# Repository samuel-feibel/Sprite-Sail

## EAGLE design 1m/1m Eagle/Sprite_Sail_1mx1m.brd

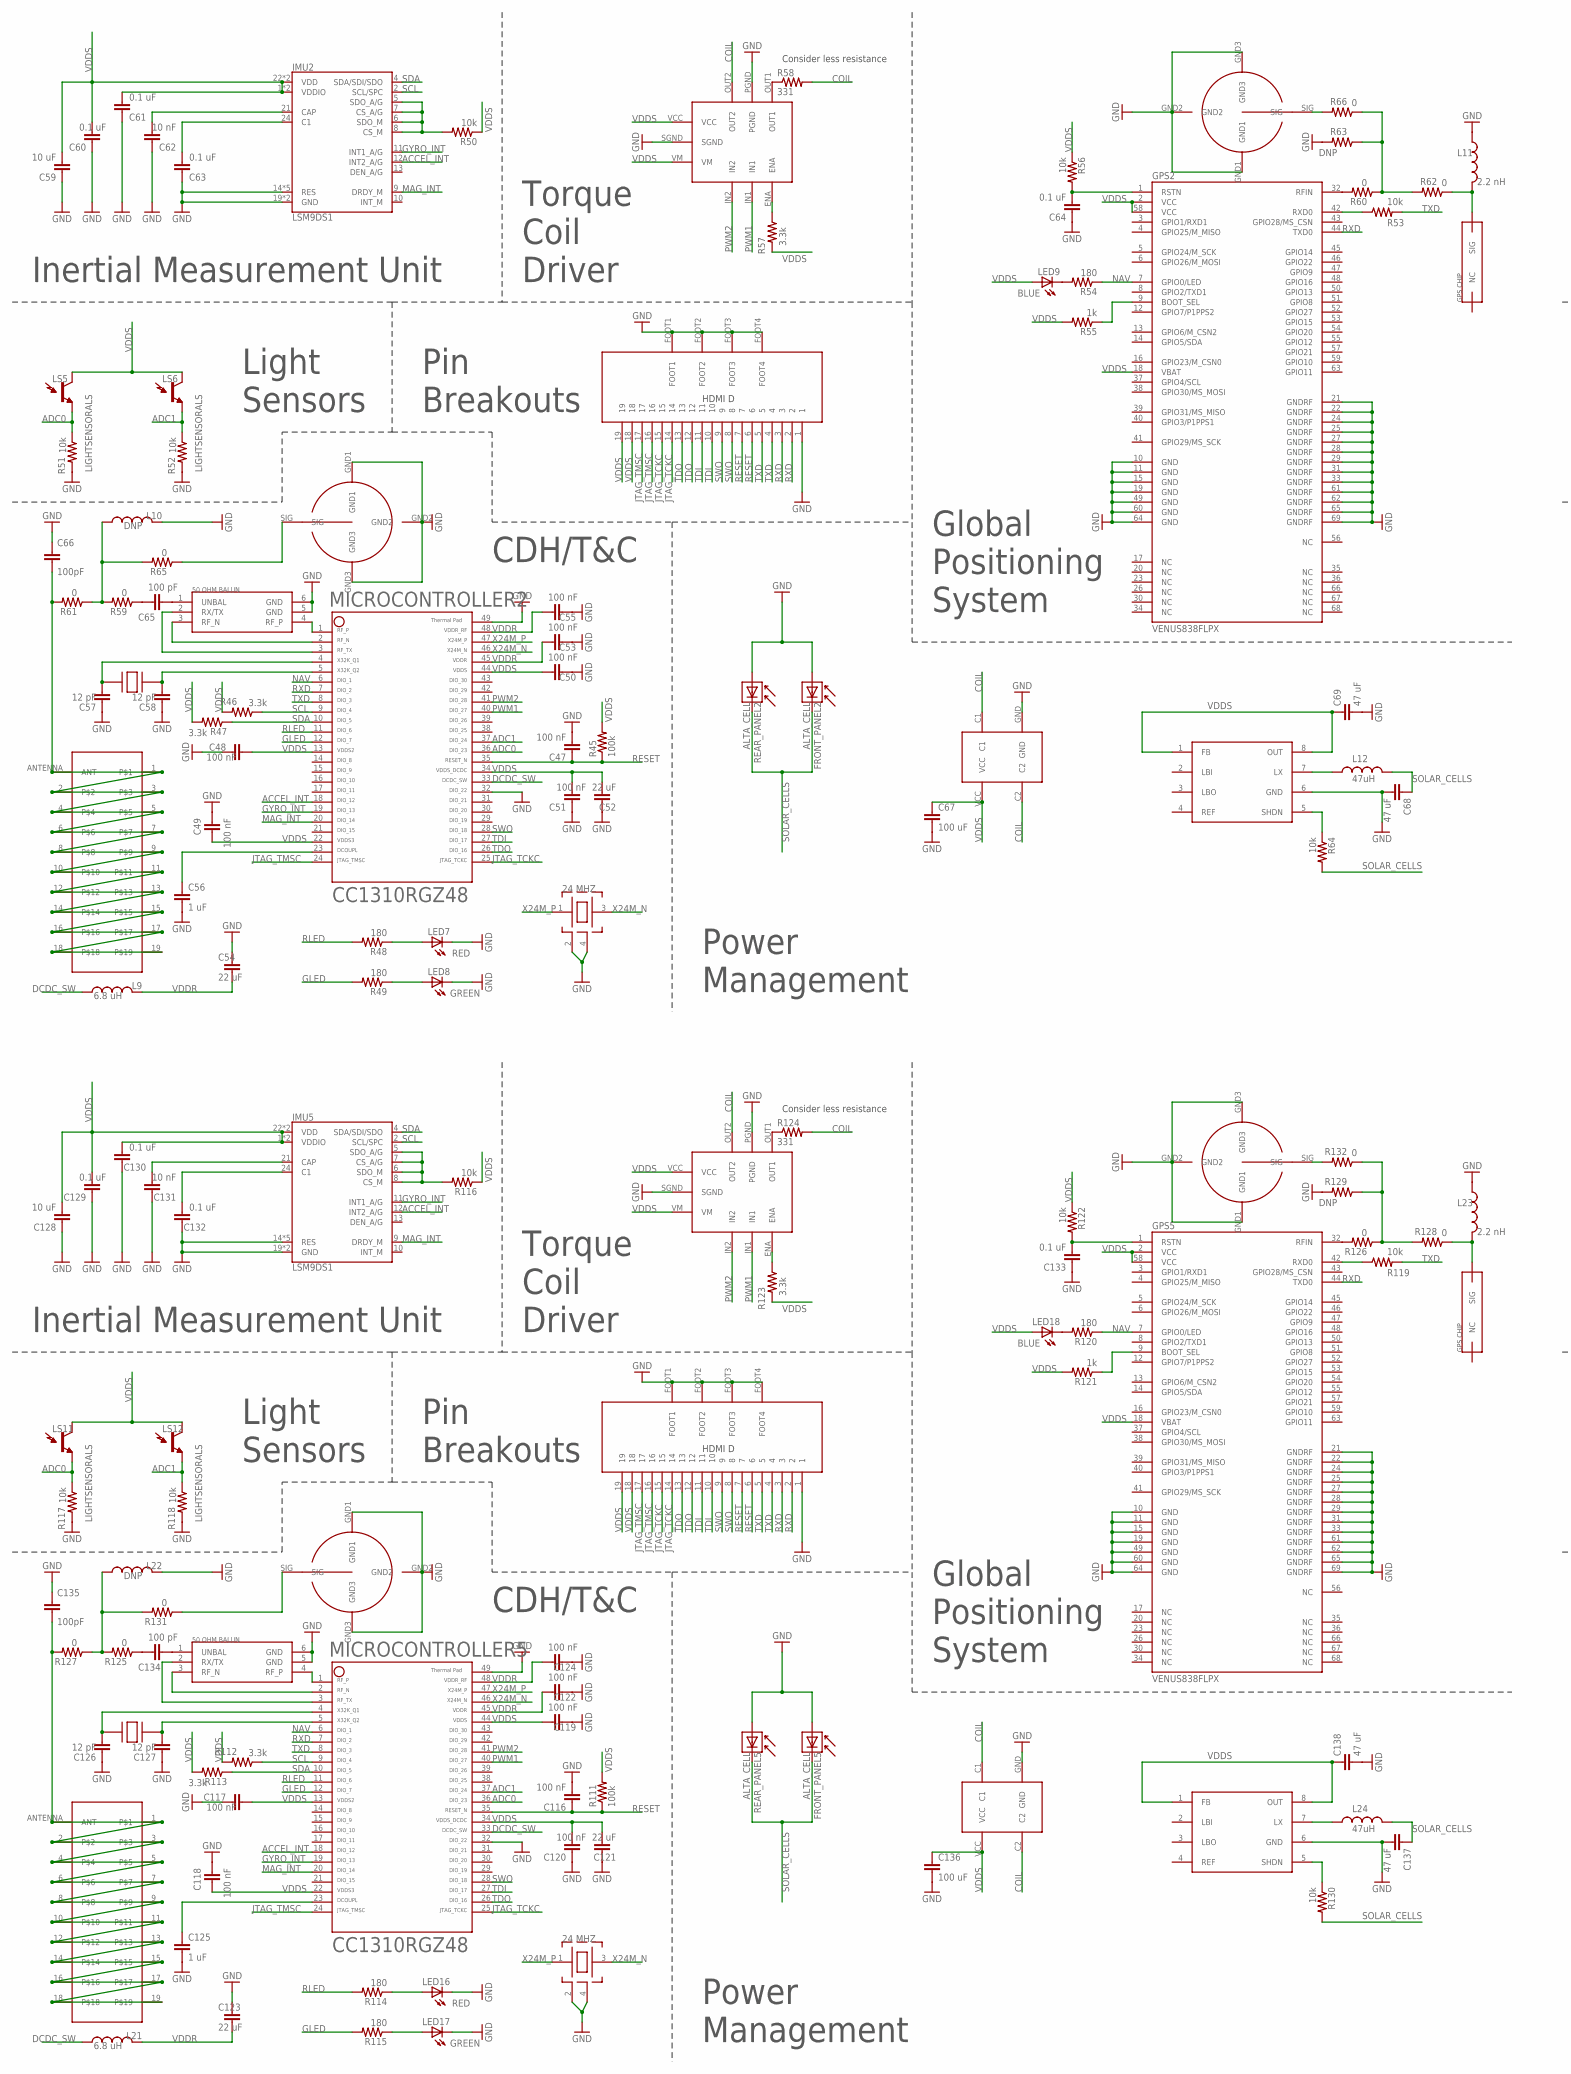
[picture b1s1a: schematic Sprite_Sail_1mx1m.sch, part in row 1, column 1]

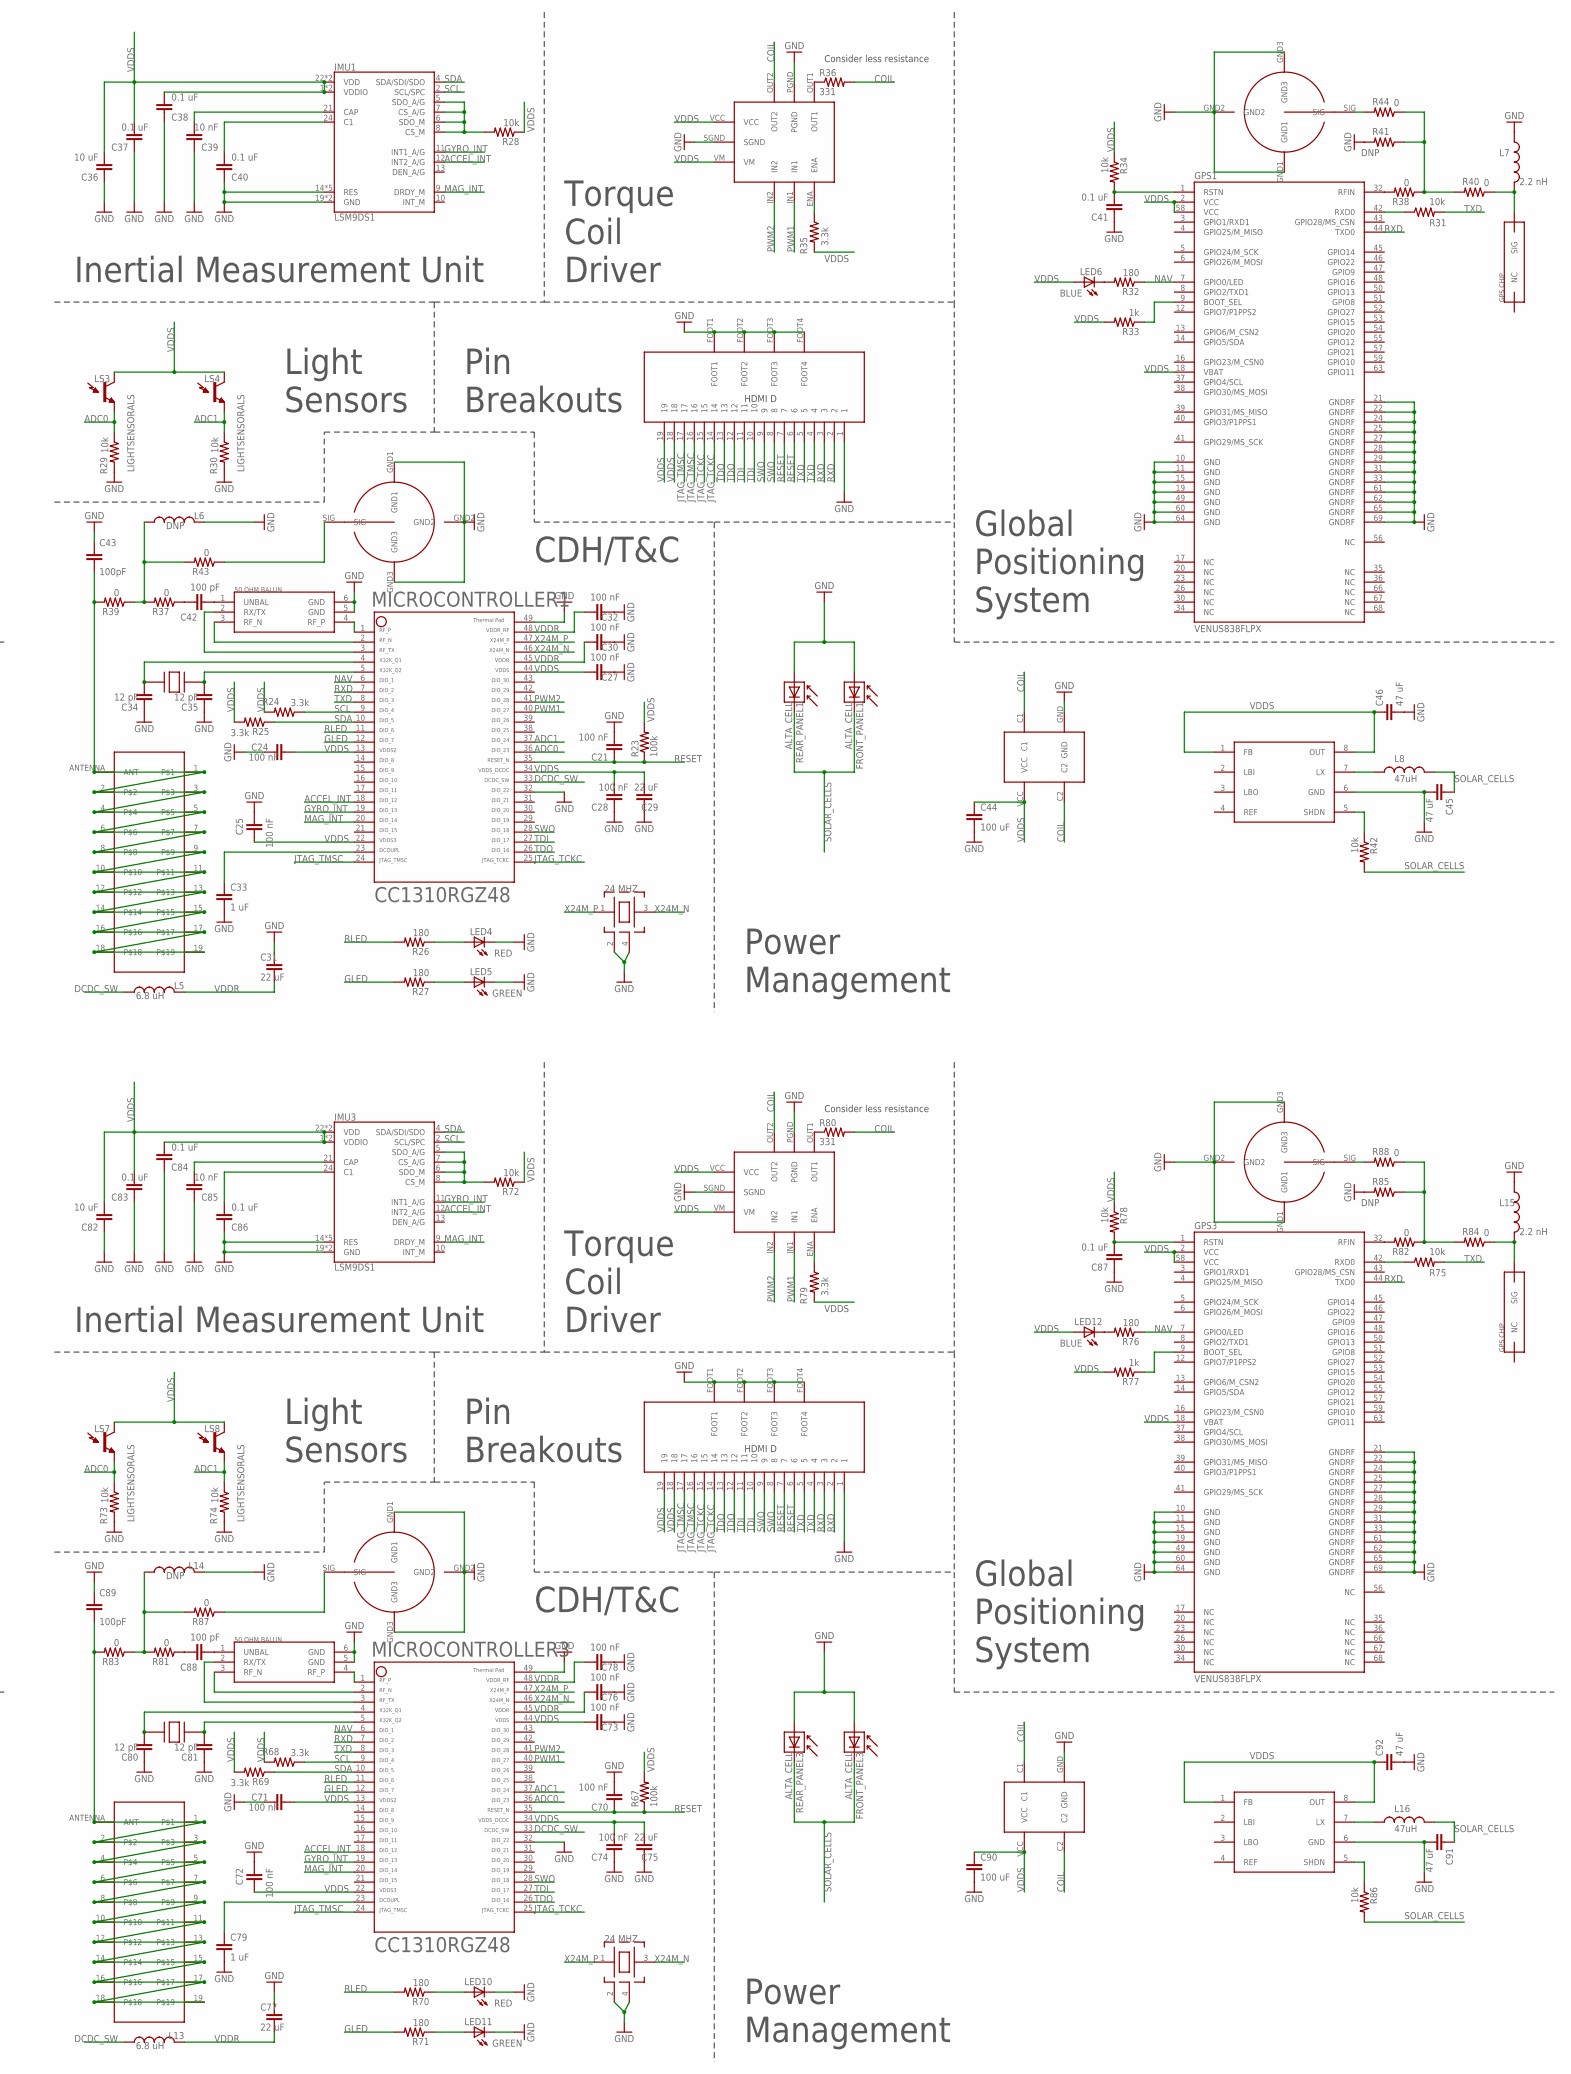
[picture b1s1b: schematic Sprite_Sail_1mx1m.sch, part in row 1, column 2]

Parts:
32.1, 32.2, 32.3, 32.5: FC-135
BALUN1, BALUN2, BALUN3, BALUN5: JOHANSON_BALUN
C21, C24, C25, C27, C28, C30, C32, C47, C48, C49, C50, C51, C53, C55, C70, C71, C72, C73, C74, C76, C78, C116, C117, C118, C119, C120, C122, C124: 100 nF; 0402-CAP
C29, C31, C52, C54, C75, C77, C121, C123: 22 uF; 0402-CAP
C33, C56, C79, C125: 1 uF; 0402-CAP
C34, C35, C57, C58, C80, C81, C126, C127: 12 pF; 0402-CAP
C36, C59, C82, C128: 10 uF; 0402-CAP
C37, C38, C40, C41, C60, C61, C63, C64, C83, C84, C86, C87, C129, C130, C132, C133: 0.1 uF; 0402-CAP
C39, C62, C85, C131: 10 nF; 0402-CAP
C42, C65, C88, C134: 100 pF; 0402-CAP
C43, C66, C89, C135: 100pF; 0603-CAP
C44, C67, C90, C136: 100 uF; 0805
C45, C46, C68, C69, C91, C92, C137, C138: 47 uF; 0805
FRONT_PANEL1, FRONT_PANEL2, FRONT_PANEL3, FRONT_PANEL5: ALTA_CELL
GPS1, GPS2, GPS3, GPS5: VENUS838FLPX
IMU1, IMU2, IMU3, IMU5: LSM9DS1; LGA24-8X4
L5, L9, L13, L21: 6.8 uH; 0603
L6, L10, L14, L22: DNP; 0603
L7, L11, L15, L23: 2.2 nH; 0603
L8, L12, L16, L24: 47uH; 0603
LED4, LED7, LED10, LED16: RED; LED-0603
LED5, LED8, LED11, LED17: GREEN; LED-0603
LED6, LED9, LED12, LED18: BLUE; LED-0603
LS3, LS4, LS5, LS6, LS7, LS8, LS11, LS12: LIGHTSENSORALS; ALS-PT19
MICROCONTROLLER1, MICROCONTROLLER2, MICROCONTROLLER3, MICROCONTROLLER5: CC1310
R23, R45, R67, R111: 100k; 0402-RES
R24, R25, R35, R46, R47, R57, R68, R69, R79, R112, R113, R123: 3.3k; 0402-RES
R26, R27, R32, R48, R49, R54, R70, R71, R76, R114, R115, R120: 180; 0402-RES
R28, R29, R30, R31, R34, R42, R50, R51, R52, R53, R56, R64, R72, R73, R74, R75, R78, R86, R116, R117, R118, R119, R122, R130: 10k; 0402-RES
R33, R55, R77, R121: 1k; 0402-RES
R36, R58, R80, R124: 331; 0402-RES
R37, R38, R39, R40, R43, R44, R59, R60, R61, R62, R65, R66, R81, R82, R83, R84, R87, R88, R125, R126, R127, R128, R131, R132: 0; 0603-RES
R41, R63, R85, R129: DNP; 0603-RES
REAR_PANEL1, REAR_PANEL2, REAR_PANEL3, REAR_PANEL5: ALTA_CELL
TSX1, TSX2, TSX3, TSX5: TSX-3225
U$1, U$17, U$25, U$41: LV8417CS
U$10, U$18, U$26, U$42: JOHANSON_GPS_CHIP
U$11, U$19, U$27, U$43: PANASONIC_RECTIFIER
U$12, U$20, U$28, U$44: PCB_ANTENNA
U$13, U$14, U$21, U$22, U$29, U$30, U$45, U$46: MM5329-2700; MM5829-2700
U$15, U$23, U$31, U$47: L6920
U$16, U$24, U$32, U$48: HDMID

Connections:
ACCEL_INT: IMU1.12 (INT2_A/G), IMU2.12 (INT2_A/G), IMU3.12 (INT2_A/G), IMU5.12 (INT2_A/G), MICROCONTROLLER1.18, MICROCONTROLLER2.18, MICROCONTROLLER3.18, MICROCONTROLLER5.18
ADC0: LS3.E (E1), LS5.E (E1), LS7.E (E1), LS11.E (E1), MICROCONTROLLER1.36, MICROCONTROLLER2.36, MICROCONTROLLER3.36, MICROCONTROLLER5.36, R29.1, R51.1, R73.1, R117.1
ADC1: LS4.E (E1), LS6.E (E1), LS8.E (E1), LS12.E (E1), MICROCONTROLLER1.37, MICROCONTROLLER2.37, MICROCONTROLLER3.37, MICROCONTROLLER5.37, R30.1, R52.1, R74.1, R118.1
ANTENNA1: C43.2, R39.2, U$12.1, U$12.2, U$12.3, U$12.4, U$12.5, U$12.6, U$12.7, U$12.8, U$12.9, U$12.10, U$12.11, U$12.12, U$12.13, U$12.14, U$12.15, U$12.16, U$12.17, U$12.18, U$12.19, U$12.ANTENNA (ANT)
ANTENNA2: C66.2, R61.2, U$20.1, U$20.2, U$20.3, U$20.4, U$20.5, U$20.6, U$20.7, U$20.8, U$20.9, U$20.10, U$20.11, U$20.12, U$20.13, U$20.14, U$20.15, U$20.16, U$20.17, U$20.18, U$20.19, U$20.ANTENNA (ANT)
ANTENNA3: C89.2, R83.2, U$28.1, U$28.2, U$28.3, U$28.4, U$28.5, U$28.6, U$28.7, U$28.8, U$28.9, U$28.10, U$28.11, U$28.12, U$28.13, U$28.14, U$28.15, U$28.16, U$28.17, U$28.18, U$28.19, U$28.ANTENNA (ANT)
ANTENNA5: C135.2, R127.2, U$44.1, U$44.2, U$44.3, U$44.4, U$44.5, U$44.6, U$44.7, U$44.8, U$44.9, U$44.10, U$44.11, U$44.12, U$44.13, U$44.14, U$44.15, U$44.16, U$44.17, U$44.18, U$44.19, U$44.ANTENNA (ANT)
COIL: R36.2, R58.2, R80.2, R124.2, U$1.OUT2, U$11.C1, U$11.C2, U$17.OUT2, U$19.C1, U$19.C2, U$25.OUT2, U$27.C1, U$27.C2, U$41.OUT2, U$43.C1, U$43.C2
DCDC_SW: L5.1, L9.1, L13.1, L21.1, MICROCONTROLLER1.33, MICROCONTROLLER2.33, MICROCONTROLLER3.33, MICROCONTROLLER5.33
GLED: MICROCONTROLLER1.12, MICROCONTROLLER2.12, MICROCONTROLLER3.12, MICROCONTROLLER5.12, R27.2, R49.2, R71.2, R115.2
GND: BALUN1.5 (GND), BALUN1.6 (GND), BALUN2.5 (GND), BALUN2.6 (GND), BALUN3.5 (GND), BALUN3.6 (GND), BALUN5.5 (GND), BALUN5.6 (GND), C21.2, C24.2, C25.2, C27.2, C28.2, C29.2, C30.2, C31.2, C32.2, C33.2, C34.2, C35.2, C36.2, C37.2, C38.2, C39.2, C40.2, C41.2, C43.1, C44.2, C45.2, C46.2, C47.2, C48.2, C49.2, C50.2, C51.2, C52.2, C53.2, C54.2, C55.2, C56.2, C57.2, C58.2, C59.2, C60.2, C61.2, C62.2, C63.2, C64.2, C66.1, C67.2, C68.2, C69.2, C70.2, C71.2, C72.2, C73.2, C74.2, C75.2, C76.2, C77.2, C78.2, C79.2, C80.2, C81.2, C82.2, C83.2, C84.2, C85.2, C86.2, C87.2, C89.1, C90.2, C91.2, C92.2, C116.2, C117.2, C118.2, C119.2, C120.2, C121.2, C122.2, C123.2, C124.2, C125.2, C126.2, C127.2, C128.2, C129.2, C130.2, C131.2, C132.2, C133.2, C135.1, C136.2, C137.2, C138.2, FRONT_PANEL1.-, FRONT_PANEL2.-, FRONT_PANEL3.-, FRONT_PANEL5.-, GPS1.10 (GND), GPS1.11 (GND), GPS1.15 (GND), GPS1.19 (GND), GPS1.21 (GNDRF), GPS1.22 (GNDRF), GPS1.24 (GNDRF), GPS1.25 (GNDRF), GPS1.27 (GNDRF), GPS1.28 (GNDRF), GPS1.29 (GNDRF), GPS1.31 (GNDRF), GPS1.33 (GNDRF), GPS1.49 (GND), GPS1.60 (GND), GPS1.61 (GNDRF), GPS1.62 (GNDRF), GPS1.64 (GND), GPS1.65 (GNDRF), GPS1.69 (GNDRF), GPS2.10 (GND), GPS2.11 (GND), GPS2.15 (GND), GPS2.19 (GND), GPS2.21 (GNDRF), GPS2.22 (GNDRF), GPS2.24 (GNDRF), GPS2.25 (GNDRF), GPS2.27 (GNDRF), GPS2.28 (GNDRF), GPS2.29 (GNDRF), GPS2.31 (GNDRF), GPS2.33 (GNDRF), GPS2.49 (GND), GPS2.60 (GND), GPS2.61 (GNDRF), GPS2.62 (GNDRF), GPS2.64 (GND), GPS2.65 (GNDRF), GPS2.69 (GNDRF), GPS3.10 (GND), GPS3.11 (GND), GPS3.15 (GND), GPS3.19 (GND), GPS3.21 (GNDRF), GPS3.22 (GNDRF), GPS3.24 (GNDRF), GPS3.25 (GNDRF), GPS3.27 (GNDRF), GPS3.28 (GNDRF), GPS3.29 (GNDRF), GPS3.31 (GNDRF), GPS3.33 (GNDRF), GPS3.49 (GND), GPS3.60 (GND), GPS3.61 (GNDRF), GPS3.62 (GNDRF), GPS3.64 (GND), GPS3.65 (GNDRF), GPS3.69 (GNDRF), GPS5.10 (GND), GPS5.11 (GND), GPS5.15 (GND), GPS5.19 (GND), GPS5.21 (GNDRF), GPS5.22 (GNDRF), GPS5.24 (GNDRF), GPS5.25 (GNDRF), GPS5.27 (GNDRF), GPS5.28 (GNDRF), GPS5.29 (GNDRF), GPS5.31 (GNDRF), GPS5.33 (GNDRF), GPS5.49 (GND), GPS5.60 (GND), GPS5.61 (GNDRF), GPS5.62 (GNDRF), GPS5.64 (GND), GPS5.65 (GNDRF), GPS5.69 (GNDRF), IMU1.14 (RES), IMU1.15 (RES), IMU1.16 (RES), IMU1.17 (RES), IMU1.18 (RES), IMU1.19 (GND), IMU1.20 (GND), IMU2.14 (RES), IMU2.15 (RES), IMU2.16 (RES), IMU2.17 (RES), IMU2.18 (RES), IMU2.19 (GND), IMU2.20 (GND), IMU3.14 (RES), IMU3.15 (RES), IMU3.16 (RES), IMU3.17 (RES), IMU3.18 (RES), IMU3.19 (GND), IMU3.20 (GND), IMU5.14 (RES), IMU5.15 (RES), IMU5.16 (RES), IMU5.17 (RES), IMU5.18 (RES), IMU5.19 (GND), IMU5.20 (GND), L6.2, L7.1, L10.2, L11.1, L14.2, L15.1, L22.2, L23.1, LED4.C, LED5.C, LED7.C, LED8.C, LED10.C, LED11.C, LED16.C, LED17.C, MICROCONTROLLER1.32, MICROCONTROLLER1.49, MICROCONTROLLER2.32, MICROCONTROLLER2.49, MICROCONTROLLER3.32, MICROCONTROLLER3.49, MICROCONTROLLER5.32, MICROCONTROLLER5.49, R29.2, R30.2, R41.2, R51.2, R52.2, R63.2, R73.2, R74.2, R85.2, R117.2, R118.2, R129.2, REAR_PANEL1.-, REAR_PANEL2.-, REAR_PANEL3.-, REAR_PANEL5.-, TSX1.2, TSX1.4, TSX2.2, TSX2.4, TSX3.2, TSX3.4, TSX5.2, TSX5.4, U$1.PGND, U$1.SGND, U$11.GND, U$13.GND1, U$13.GND2, U$13.GND3, U$14.GND1, U$14.GND2, U$14.GND3, U$15.6 (GND), U$16.1, U$16.FOOT1, U$16.FOOT2, U$16.FOOT3, U$16.FOOT4, U$17.PGND, U$17.SGND, U$19.GND, U$21.GND1, U$21.GND2, U$21.GND3, U$22.GND1, U$22.GND2, U$22.GND3, U$23.6 (GND), U$24.1, U$24.FOOT1, U$24.FOOT2, U$24.FOOT3, U$24.FOOT4, U$25.PGND, U$25.SGND, U$27.GND, U$29.GND1, U$29.GND2, U$29.GND3, U$30.GND1, U$30.GND2, U$30.GND3, U$31.6 (GND), U$32.1, U$32.FOOT1, U$32.FOOT2, U$32.FOOT3, U$32.FOOT4, U$41.PGND, U$41.SGND, U$43.GND, U$45.GND1, U$45.GND2, U$45.GND3, U$46.GND1, U$46.GND2, U$46.GND3, U$47.6 (GND), U$48.1, U$48.FOOT1, U$48.FOOT2, U$48.FOOT3, U$48.FOOT4
GYRO_INT: IMU1.11 (INT1_A/G), IMU2.11 (INT1_A/G), IMU3.11 (INT1_A/G), IMU5.11 (INT1_A/G), MICROCONTROLLER1.19, MICROCONTROLLER2.19, MICROCONTROLLER3.19, MICROCONTROLLER5.19
JTAG_TCKC: MICROCONTROLLER1.25, MICROCONTROLLER2.25, MICROCONTROLLER3.25, MICROCONTROLLER5.25, U$16.14, U$16.15, U$24.14, U$24.15, U$32.14, U$32.15, U$48.14, U$48.15
JTAG_TMSC: MICROCONTROLLER1.24, MICROCONTROLLER2.24, MICROCONTROLLER3.24, MICROCONTROLLER5.24, U$16.16, U$16.17, U$24.16, U$24.17, U$32.16, U$32.17, U$48.16, U$48.17
MAG_INT: IMU1.9 (DRDY_M), IMU2.9 (DRDY_M), IMU3.9 (DRDY_M), IMU5.9 (DRDY_M), MICROCONTROLLER1.20, MICROCONTROLLER2.20, MICROCONTROLLER3.20, MICROCONTROLLER5.20
unnamed: C33.1, MICROCONTROLLER1.23
unnamed: 32.1.P2, C34.1, MICROCONTROLLER1.4
unnamed: 32.1.P1, C35.1, MICROCONTROLLER1.5
unnamed: LED4.A, R26.1
unnamed: LED5.A, R27.1
unnamed: C39.1, IMU1.21 (CAP)
unnamed: C40.1, IMU1.24 (C1)
unnamed: IMU1.5 (SDO_A/G), IMU1.6 (SDO_M), IMU1.7 (CS_A/G), IMU1.8 (CS_M), R28.2
unnamed: GPS1.42 (RXD0), R31.1
unnamed: LED6.C, R32.2
unnamed: GPS1.9 (BOOT_SEL), R33.1
unnamed: C41.1, GPS1.1 (RSTN), R34.2
unnamed: R35.1, U$1.ENA
unnamed: R36.1, U$1.OUT1
unnamed: BALUN1.4 (RF_P), MICROCONTROLLER1.1
unnamed: BALUN1.3 (RF_N), MICROCONTROLLER1.2
unnamed: BALUN1.2 (RX/TX), MICROCONTROLLER1.3
unnamed: BALUN1.1 (UNBAL), C42.2
unnamed: L6.1, R37.2, R39.1, R43.2
unnamed: C42.1, R37.1
unnamed: GPS1.32 (RFIN), R38.2
unnamed: R38.1, R40.2, R41.1, R44.1
unnamed: L7.2, R40.1, U$10.SIG
unnamed: R42.1, U$15.5 (SHDN)
unnamed: L8.1, U$15.7 (LX)
unnamed: R44.2, U$14.SIG
unnamed: R43.1, U$13.SIG
unnamed: C56.1, MICROCONTROLLER2.23
unnamed: 32.2.P2, C57.1, MICROCONTROLLER2.4
unnamed: 32.2.P1, C58.1, MICROCONTROLLER2.5
unnamed: LED7.A, R48.1
unnamed: LED8.A, R49.1
unnamed: C62.1, IMU2.21 (CAP)
unnamed: C63.1, IMU2.24 (C1)
unnamed: IMU2.5 (SDO_A/G), IMU2.6 (SDO_M), IMU2.7 (CS_A/G), IMU2.8 (CS_M), R50.2
unnamed: GPS2.42 (RXD0), R53.1
unnamed: LED9.C, R54.2
unnamed: GPS2.9 (BOOT_SEL), R55.1
unnamed: C64.1, GPS2.1 (RSTN), R56.2
unnamed: R57.1, U$17.ENA
unnamed: R58.1, U$17.OUT1
unnamed: BALUN2.4 (RF_P), MICROCONTROLLER2.1
unnamed: BALUN2.3 (RF_N), MICROCONTROLLER2.2
unnamed: BALUN2.2 (RX/TX), MICROCONTROLLER2.3
unnamed: BALUN2.1 (UNBAL), C65.2
unnamed: L10.1, R59.2, R61.1, R65.2
unnamed: C65.1, R59.1
unnamed: GPS2.32 (RFIN), R60.2
unnamed: R60.1, R62.2, R63.1, R66.1
unnamed: L11.2, R62.1, U$18.SIG
unnamed: R64.1, U$23.5 (SHDN)
unnamed: L12.1, U$23.7 (LX)
unnamed: R66.2, U$22.SIG
unnamed: R65.1, U$21.SIG
unnamed: C79.1, MICROCONTROLLER3.23
unnamed: 32.3.P2, C80.1, MICROCONTROLLER3.4
unnamed: 32.3.P1, C81.1, MICROCONTROLLER3.5
unnamed: LED10.A, R70.1
unnamed: LED11.A, R71.1
unnamed: C85.1, IMU3.21 (CAP)
unnamed: C86.1, IMU3.24 (C1)
unnamed: IMU3.5 (SDO_A/G), IMU3.6 (SDO_M), IMU3.7 (CS_A/G), IMU3.8 (CS_M), R72.2
unnamed: GPS3.42 (RXD0), R75.1
unnamed: LED12.C, R76.2
unnamed: GPS3.9 (BOOT_SEL), R77.1
unnamed: C87.1, GPS3.1 (RSTN), R78.2
unnamed: R79.1, U$25.ENA
unnamed: R80.1, U$25.OUT1
unnamed: BALUN3.4 (RF_P), MICROCONTROLLER3.1
unnamed: BALUN3.3 (RF_N), MICROCONTROLLER3.2
unnamed: BALUN3.2 (RX/TX), MICROCONTROLLER3.3
unnamed: BALUN3.1 (UNBAL), C88.2
unnamed: L14.1, R81.2, R83.1, R87.2
unnamed: C88.1, R81.1
unnamed: GPS3.32 (RFIN), R82.2
unnamed: R82.1, R84.2, R85.1, R88.1
unnamed: L15.2, R84.1, U$26.SIG
unnamed: R86.1, U$31.5 (SHDN)
unnamed: L16.1, U$31.7 (LX)
unnamed: R88.2, U$30.SIG
unnamed: R87.1, U$29.SIG
unnamed: C125.1, MICROCONTROLLER5.23
unnamed: 32.5.P2, C126.1, MICROCONTROLLER5.4
unnamed: 32.5.P1, C127.1, MICROCONTROLLER5.5
unnamed: LED16.A, R114.1
unnamed: LED17.A, R115.1
unnamed: C131.1, IMU5.21 (CAP)
unnamed: C132.1, IMU5.24 (C1)
unnamed: IMU5.5 (SDO_A/G), IMU5.6 (SDO_M), IMU5.7 (CS_A/G), IMU5.8 (CS_M), R116.2
unnamed: GPS5.42 (RXD0), R119.1
unnamed: LED18.C, R120.2
unnamed: GPS5.9 (BOOT_SEL), R121.1
unnamed: C133.1, GPS5.1 (RSTN), R122.2
unnamed: R123.1, U$41.ENA
unnamed: R124.1, U$41.OUT1
unnamed: BALUN5.4 (RF_P), MICROCONTROLLER5.1
unnamed: BALUN5.3 (RF_N), MICROCONTROLLER5.2
unnamed: BALUN5.2 (RX/TX), MICROCONTROLLER5.3
unnamed: BALUN5.1 (UNBAL), C134.2
unnamed: L22.1, R125.2, R127.1, R131.2
unnamed: C134.1, R125.1
unnamed: GPS5.32 (RFIN), R126.2
unnamed: R126.1, R128.2, R129.1, R132.1
unnamed: L23.2, R128.1, U$42.SIG
unnamed: R130.1, U$47.5 (SHDN)
unnamed: L24.1, U$47.7 (LX)
unnamed: R132.2, U$46.SIG
unnamed: R131.1, U$45.SIG
NAV: GPS1.7 (GPIO0/LED), GPS2.7 (GPIO0/LED), GPS3.7 (GPIO0/LED), GPS5.7 (GPIO0/LED), MICROCONTROLLER1.6, MICROCONTROLLER2.6, MICROCONTROLLER3.6, MICROCONTROLLER5.6, R32.1, R54.1, R76.1, R120.1
PWM1: MICROCONTROLLER1.40, MICROCONTROLLER2.40, MICROCONTROLLER3.40, MICROCONTROLLER5.40, U$1.IN1, U$17.IN1, U$25.IN1, U$41.IN1
PWM2: MICROCONTROLLER1.41, MICROCONTROLLER2.41, MICROCONTROLLER3.41, MICROCONTROLLER5.41, U$1.IN2, U$17.IN2, U$25.IN2, U$41.IN2
RESET: C21.1, C47.1, C70.1, C116.1, MICROCONTROLLER1.35, MICROCONTROLLER2.35, MICROCONTROLLER3.35, MICROCONTROLLER5.35, R23.1, R45.1, R67.1, R111.1, U$16.6, U$16.7, U$24.6, U$24.7, U$32.6, U$32.7, U$48.6, U$48.7
RLED: MICROCONTROLLER1.11, MICROCONTROLLER2.11, MICROCONTROLLER3.11, MICROCONTROLLER5.11, R26.2, R48.2, R70.2, R114.2
RXD: GPS1.44 (TXD0), GPS2.44 (TXD0), GPS3.44 (TXD0), GPS5.44 (TXD0), MICROCONTROLLER1.7, MICROCONTROLLER2.7, MICROCONTROLLER3.7, MICROCONTROLLER5.7, U$16.2, U$16.3, U$24.2, U$24.3, U$32.2, U$32.3, U$48.2, U$48.3
SCL: IMU1.2 (SCL/SPC), IMU2.2 (SCL/SPC), IMU3.2 (SCL/SPC), IMU5.2 (SCL/SPC), MICROCONTROLLER1.9, MICROCONTROLLER2.9, MICROCONTROLLER3.9, MICROCONTROLLER5.9, R24.1, R46.1, R68.1, R112.1
SDA: IMU1.4 (SDA/SDI/SDO), IMU2.4 (SDA/SDI/SDO), IMU3.4 (SDA/SDI/SDO), IMU5.4 (SDA/SDI/SDO), MICROCONTROLLER1.10, MICROCONTROLLER2.10, MICROCONTROLLER3.10, MICROCONTROLLER5.10, R25.1, R47.1, R69.1, R113.1
SOLAR_CELLS: C45.1, C68.1, C91.1, C137.1, FRONT_PANEL1.+, FRONT_PANEL2.+, FRONT_PANEL3.+, FRONT_PANEL5.+, L8.2, L12.2, L16.2, L24.2, R42.2, R64.2, R86.2, R130.2, REAR_PANEL1.+, REAR_PANEL2.+, REAR_PANEL3.+, REAR_PANEL5.+
SWO: MICROCONTROLLER1.28, MICROCONTROLLER2.28, MICROCONTROLLER3.28, MICROCONTROLLER5.28, U$16.8, U$16.9, U$24.8, U$24.9, U$32.8, U$32.9, U$48.8, U$48.9
TDI: MICROCONTROLLER1.27, MICROCONTROLLER2.27, MICROCONTROLLER3.27, MICROCONTROLLER5.27, U$16.10, U$16.11, U$24.10, U$24.11, U$32.10, U$32.11, U$48.10, U$48.11
TDO: MICROCONTROLLER1.26, MICROCONTROLLER2.26, MICROCONTROLLER3.26, MICROCONTROLLER5.26, U$16.12, U$16.13, U$24.12, U$24.13, U$32.12, U$32.13, U$48.12, U$48.13
TXD: MICROCONTROLLER1.8, MICROCONTROLLER2.8, MICROCONTROLLER3.8, MICROCONTROLLER5.8, R31.2, R53.2, R75.2, R119.2, U$16.4, U$16.5, U$24.4, U$24.5, U$32.4, U$32.5, U$48.4, U$48.5
VDDR: C30.1, C31.1, C32.1, C53.1, C54.1, C55.1, C76.1, C77.1, C78.1, C122.1, C123.1, C124.1, L5.2, L9.2, L13.2, L21.2, MICROCONTROLLER1.45, MICROCONTROLLER1.48, MICROCONTROLLER2.45, MICROCONTROLLER2.48, MICROCONTROLLER3.45, MICROCONTROLLER3.48, MICROCONTROLLER5.45, MICROCONTROLLER5.48
VDDS: C24.1, C25.1, C27.1, C28.1, C29.1, C36.1, C37.1, C38.1, C44.1, C46.1, C48.1, C49.1, C50.1, C51.1, C52.1, C59.1, C60.1, C61.1, C67.1, C69.1, C71.1, C72.1, C73.1, C74.1, C75.1, C82.1, C83.1, C84.1, C90.1, C92.1, C117.1, C118.1, C119.1, C120.1, C121.1, C128.1, C129.1, C130.1, C136.1, C138.1, GPS1.2 (VCC), GPS1.18 (VBAT), GPS1.58 (VCC), GPS2.2 (VCC), GPS2.18 (VBAT), GPS2.58 (VCC), GPS3.2 (VCC), GPS3.18 (VBAT), GPS3.58 (VCC), GPS5.2 (VCC), GPS5.18 (VBAT), GPS5.58 (VCC), IMU1.1 (VDDIO), IMU1.3 (VDDIO), IMU1.22 (VDD), IMU1.23 (VDD), IMU2.1 (VDDIO), IMU2.3 (VDDIO), IMU2.22 (VDD), IMU2.23 (VDD), IMU3.1 (VDDIO), IMU3.3 (VDDIO), IMU3.22 (VDD), IMU3.23 (VDD), IMU5.1 (VDDIO), IMU5.3 (VDDIO), IMU5.22 (VDD), IMU5.23 (VDD), LED6.A, LED9.A, LED12.A, LED18.A, LS3.C (C1), LS4.C (C1), LS5.C (C1), LS6.C (C1), LS7.C (C1), LS8.C (C1), LS11.C (C1), LS12.C (C1), MICROCONTROLLER1.13, MICROCONTROLLER1.22, MICROCONTROLLER1.34, MICROCONTROLLER1.44, MICROCONTROLLER2.13, MICROCONTROLLER2.22, MICROCONTROLLER2.34, MICROCONTROLLER2.44, MICROCONTROLLER3.13, MICROCONTROLLER3.22, MICROCONTROLLER3.34, MICROCONTROLLER3.44, MICROCONTROLLER5.13, MICROCONTROLLER5.22, MICROCONTROLLER5.34, MICROCONTROLLER5.44, R23.2, R24.2, R25.2, R28.1, R33.2, R34.1, R35.2, R45.2, R46.2, R47.2, R50.1, R55.2, R56.1, R57.2, R67.2, R68.2, R69.2, R72.1, R77.2, R78.1, R79.2, R111.2, R112.2, R113.2, R116.1, R121.2, R122.1, R123.2, U$1.VCC, U$1.VM, U$11.VCC, U$15.1 (FB), U$15.8 (OUT), U$16.18, U$16.19, U$17.VCC, U$17.VM, U$19.VCC, U$23.1 (FB), U$23.8 (OUT), U$24.18, U$24.19, U$25.VCC, U$25.VM, U$27.VCC, U$31.1 (FB), U$31.8 (OUT), U$32.18, U$32.19, U$41.VCC, U$41.VM, U$43.VCC, U$47.1 (FB), U$47.8 (OUT), U$48.18, U$48.19
X24M_N: MICROCONTROLLER1.46, MICROCONTROLLER2.46, MICROCONTROLLER3.46, MICROCONTROLLER5.46, TSX1.3, TSX2.3, TSX3.3, TSX5.3
X24M_P: MICROCONTROLLER1.47, MICROCONTROLLER2.47, MICROCONTROLLER3.47, MICROCONTROLLER5.47, TSX1.1, TSX2.1, TSX3.1, TSX5.1

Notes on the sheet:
CDH/T&C
Inertial Measurement Unit
Power Management
Light Sensors
Global Positioning System
Pin Breakouts
Torque Coil Driver
Consider less resistance

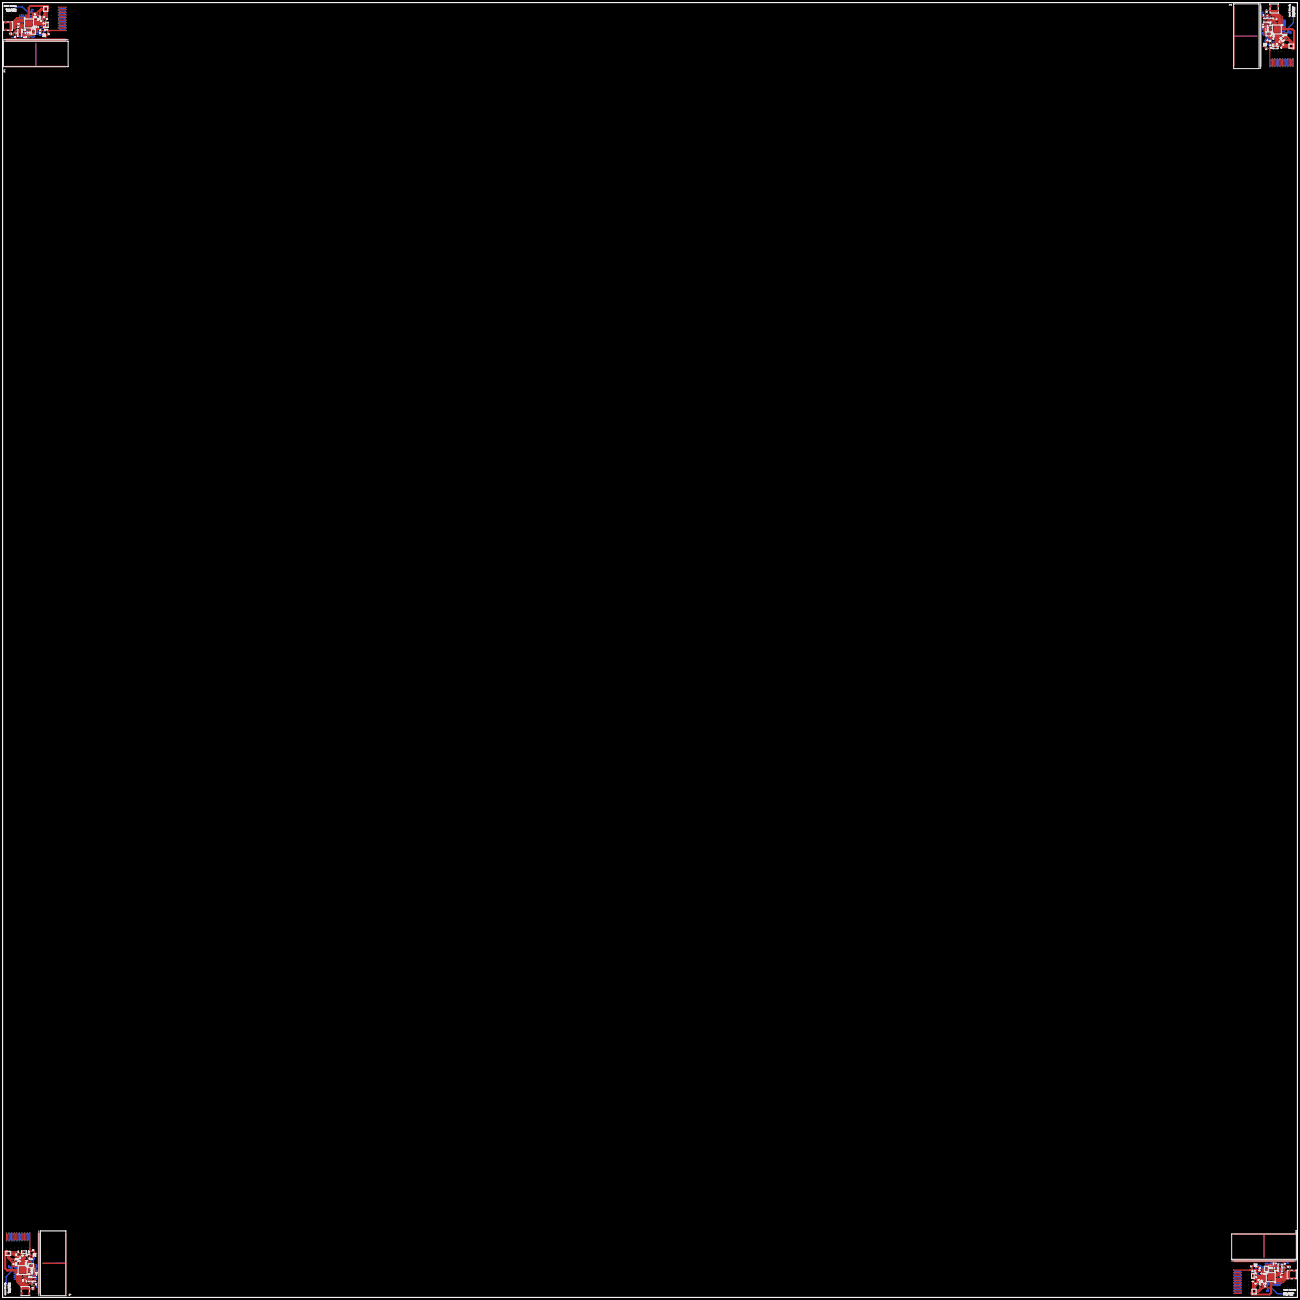
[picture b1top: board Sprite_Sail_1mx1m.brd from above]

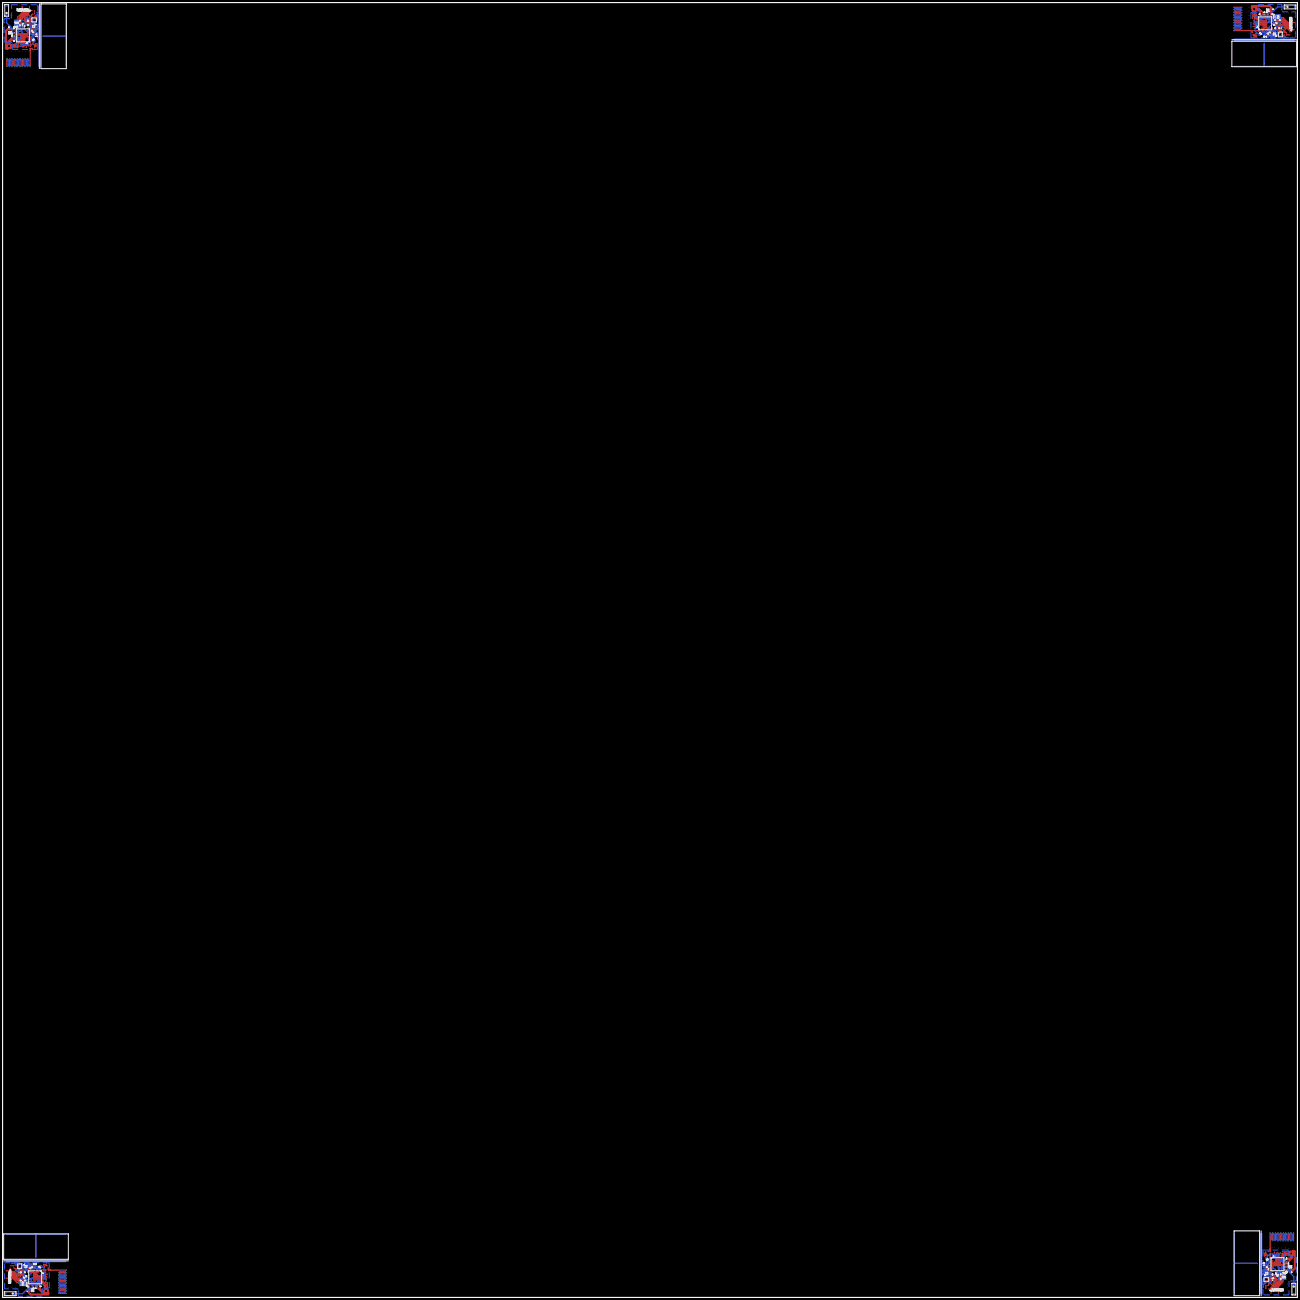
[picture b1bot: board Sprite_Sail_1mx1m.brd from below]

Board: 4 copper layers, 1000.0 x 1000.0 mm, 280 parts (124 on the bottom side), 140 nets.

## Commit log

2018-04-27 reorganized folders
2018-05-03 Add files via upload
    1m by 1m Sail Files
2018-05-03 organized between 1m and 60cm

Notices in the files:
parts and their libraries:
SparkFun: Licensing: CC v3.0 Share-Alike You are welcome to use this library for commercial purposes.
SparkFun-Sensors: Licensing: Creative Commons ShareAlike 4.0 International - https://creativecommons.org/licenses/by-sa/4.0
